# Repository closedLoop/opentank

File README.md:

# opentank
(WORK IN PROGRESS) A smart home sensor hub with ESP32-C6, rich analog capabilities, and full self-powering.
https://youtu.be/-s6jZ4U3TzU

## Design views

### Isometric 3D view

The render now uses repository-local models instead of machine-local CAD paths. U12 uses Espressif's exact manufacturer STEP model; J1, J2, and the previously missing small packages use footprint-aligned, datasheet-sized visualization models documented in [`assets/3d/README.md`](assets/3d/README.md). Confirm connector details and enclosure fit with exact manufacturer CAD before assembly release. The TH1 solder-wire footprint intentionally has no fitted component body.

### PCB top view

### PCB bottom view

### Schematic

## Changes versus `main`

These comparisons use matching KiCad layers, scale, and sheet coordinates. Magenta marks geometry present only on `main` (removed or moved), green marks geometry present only on this branch (added or moved), and gray provides unchanged context.

### PCB top comparison

### PCB bottom comparison

### Schematic comparison

## Important note

The USB D-/D+ routing and U17 SDA/SCL routing have been corrected in both the schematic and PCB. Both USB data pairs now remain on F.Cu without vias; the MCU-side pair is length tuned to 0.001 mm routed skew and assigned to a 0.127 mm / 0.150 mm USB width/gap net class targeting 90-ohm differential impedance.

The `templateforconfiguration.yaml` Home Assistant example is still somewhat broken because its current logic never reports a value below 0. `fulldevicecode.yaml` is the configuration programmed onto the PCB and has been observed running reliably for more than two months. Questions? Email rain@haaseindustries.com or comment on the linked YouTube video.

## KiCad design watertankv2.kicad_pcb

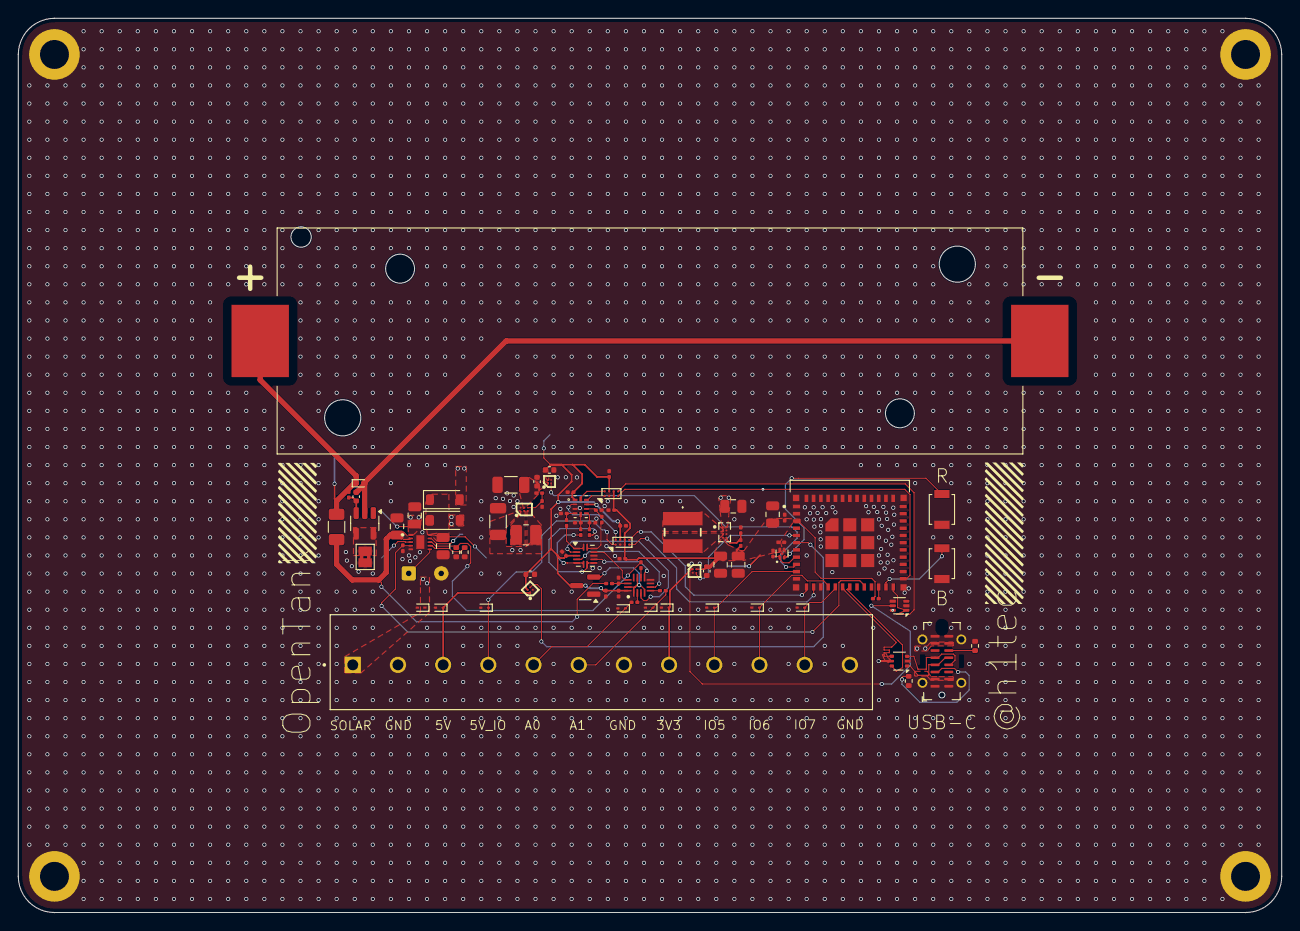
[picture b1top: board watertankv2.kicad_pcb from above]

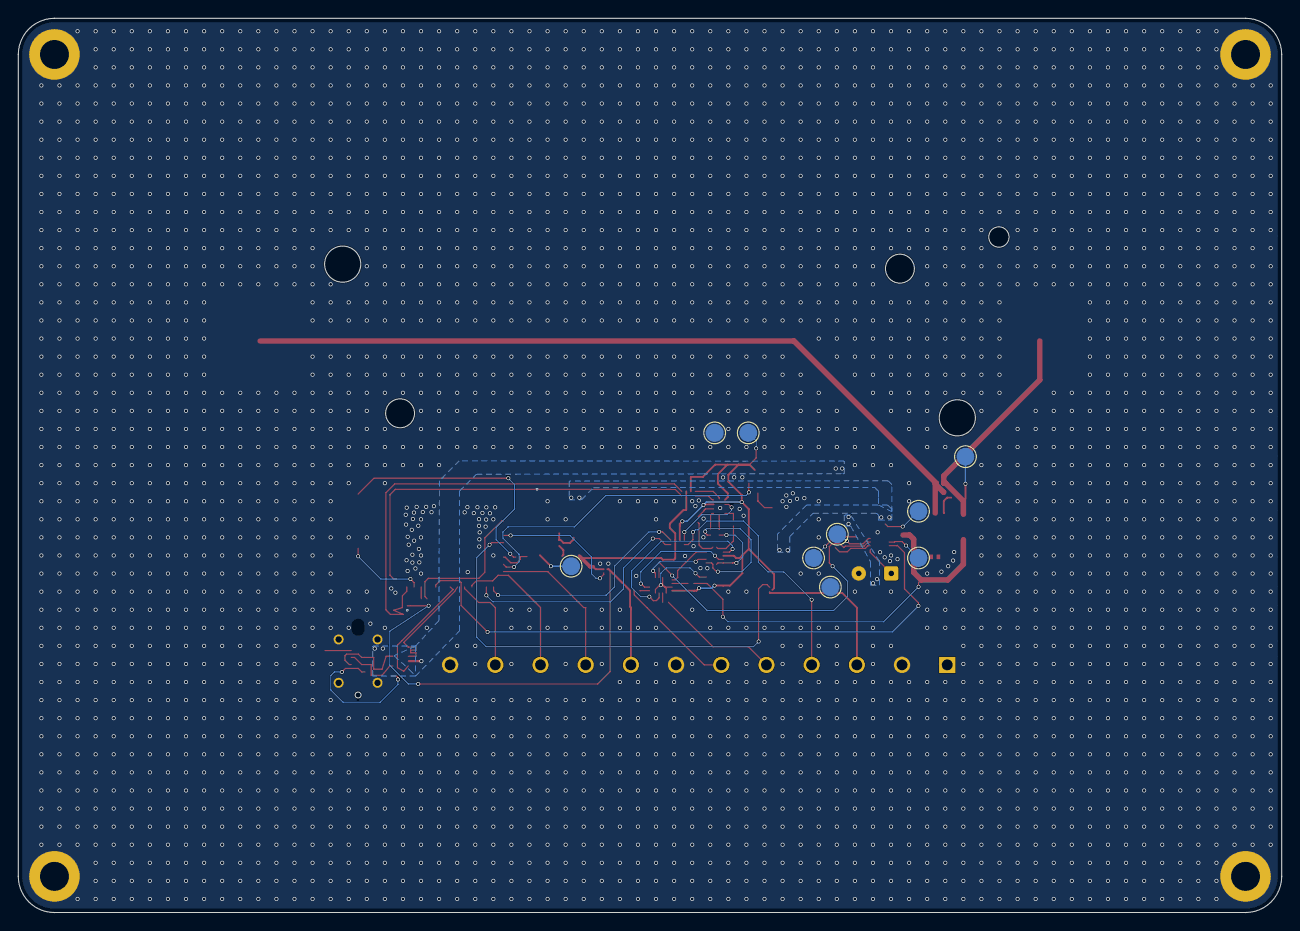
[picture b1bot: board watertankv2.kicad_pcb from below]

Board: 4 copper layers, 139.8 x 98.9 mm, 101 parts (9 on the bottom side), 69 nets.

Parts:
BT1: NMC; 21700holder
C1, C14, C15: 1u; C_0402_1005Metric
C2, C3, C4, C5, C6, C7, C23: 22u; C_0805_2012Metric
C8, C9: 10u; C_1206_3216Metric
C10, C11: 2u2; C_0402_1005Metric
C12, C13, C16, C17, C18, C19, C20, C21, C22, C24, C25, C26, C27, C28: 100n; C_0201_0603Metric
D1, D2: 20V; D_SOD-123
D3, D4, D5, D6, D7, D8, D9, D10, D11, D12: 6.5V; D_SOD-923
F1: 3A; Fuse_1206_3216Metric
H1, H2, H3, H4: 3.2mm; MountingHole_3.2mm_M3_DIN965_Pad
J1: 1792960; PHOENIX_1792960
J2: GT-USB-7051A; USB_C_Receptacle_G-Switch_GT-USB-7051x
JP1: I_SNSEXT; SolderJumper-2_P1.3mm_Bridged2Bar_Pad1.0x1.5mm
L1: 1u; 74404043010A
L2: 2u2; L_1008_2520Metric
R1, R9, R11, R12, R13: 100; R_0201_0603Metric
R2, R5, R15, R16: 511K; R_0201_0603Metric
R3: 6K8; R_0402_1005Metric
R4: 681; R_0402_1005Metric
R6: 91K; R_0201_0603Metric
R7: 1M1; R_0201_0603Metric
R8: 249K; R_0201_0603Metric
R10, R14, R17, R18, R19: 10K; R_0201_0603Metric
R23, R24: 5K1; R_0402_1005Metric
SW1: BOOT; SW_SPST_B3U-1000P
SW2: RESET; SW_SPST_B3U-1000P
TH1: 103AT; SolderWire-0.1sqmm_1x02_P3.6mm_D0.4mm_OD1mm
TP1: BQ_IN; TestPoint_Pad_D2.0mm
TP2: STAT1; TestPoint_Pad_D2.0mm
TP3: STAT2; TestPoint_Pad_D2.0mm
TP4: 3V3; TestPoint_Pad_D2.0mm
TP5, TP9: GND; TestPoint_Pad_D2.0mm
TP6: 5V; TestPoint_Pad_D2.0mm
TP7: SYS; TestPoint_Pad_D2.0mm
TP10: VBATSNS; TestPoint_Pad_D2.0mm
U1: DW03C; SOT-23-5
U2: BQ25185DLHR; IC_BQ25185DLHR
U3: TPS631010YBGR; IC_TPS631010YBGR
U4: TPS61099YFFR; BGA6C40P2X3_88X123X62
U5: TPS7A2050PYCKR; BGA4C35P2X2_62X62X33
U6, U11: TPS22916CYFPR; BGA4C40P2X2_75X75X50
U7: TMUX1511RSVR; QFN40P180X260X55-16N
U8: TLV9004IRUCR; Texas_S-PX2QFN-14
U9: TLV809EA46DBZR; SOT-23
U10: ADS1115IRUGR; IC_ADS1115IRUGR
U12: ESP32-C6-MINI-1U-N4; XCVR_ESP32-C6-MINI-1U-N4
U13, U14: LXS0102; Texas_DSBGA-8_0.9x1.9mm_Layout2x4_P0.5mm
U15: TLV803EA29DPWR; Texas_X2SON-5_0.8x0.8mm_P0.48mm
U16: USBLC6-2P6; SOT-666
U17: TMP102AIDRLR; SOT-563

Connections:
+3V3: C6.1, C7.1, C14.1, C22.2, C23.1, C24.2, C27.2, C28.2, R5.1, R18.1, R19.1, TP4.1, U3.D1 (VOUT), U6.A2 (VIN), U12.3 (3V3), U13.C1 (VCCA), U13.C2 (OE), U14.C1 (VCCA), U14.C2 (OE), U15.5 (VDD)
+5V: C11.1, C12.1, C13.1, C15.2, C20.2, C21.2, C25.2, C26.2, TP6.1, U5.A2 (OUT), U7.16 (VDD), U8.3 (V+), U9.3 (VDD), U10.1 (ADDR), U10.8 (VDD), U11.A2 (VIN), U13.B2 (VCCB), U14.B2 (VCCB)
/0: U12.12 (IO0), U14.D2 (A1)
/1: U12.13 (IO1), U14.D1 (A2)
/2: U6.B2 (ON), U12.5 (IO2)
/3: U11.B2 (ON), U12.6 (IO3)
/4: U5.B1 (EN), U12.9 (IO4)
/5: D6.1 (A1), J1.09, U12.10 (IO5)
/5V_IO: D7.1 (A1), J1.04, U14.A1 (B2)
/6: D10.1 (A1), J1.10, U12.15 (IO6)
/7: D11.1 (A1), J1.11, U12.16 (IO7)
/15: R2.1, U2.4 (~CE), U12.20 (IO15)
/18: U12.24 (IO18), U13.D2 (A1), U17.1 (SCL)
/19: U12.25 (IO19), U13.D1 (A2), U17.6 (SDA)
/ADS_0: C16.1, R9.2, U10.4 (AIN0)
/ADS_1: C17.1, R11.2, U10.5 (AIN1)
/ADS_2: C18.1, R12.2, U10.6 (AIN2)
/ADS_3: C19.1, R13.2, U10.7 (AIN3)
/ADS_A: U10.2 (ALERT/RDY), U14.A2 (B1)
/ADS_C: U10.10 (SCL), U13.A2 (B1)
/ADS_D: U10.9 (SDA), U13.A1 (B2)
/CH0: R10.2, U7.2 (S1)
/CH0_P: R9.1, U8.1 (-), U8.14
/CH1: R14.2, U7.5 (S2)
/CH1_P: R11.1, U8.5 (-), U8.6
/CH2: R17.2, U7.10 (S3)
/CH2_P: R12.1, U8.7, U8.8 (-)
/CH3: R15.2, R16.1, U7.14 (S4)
/CH3_P: R13.1, U8.12 (-), U8.13
/D+: J2.A6 (D+), J2.B6 (D+), U16.1 (I/O1)
/D-: J2.A7 (D-), J2.B7 (D-), U16.3 (I/O2)
/D_N: U12.17 (IO12), U16.4 (I/O2)
/D_P: U12.18 (IO13), U16.6 (I/O1)
/IN0: D8.1 (A1), J1.05, R10.1
/IN1: D4.1 (A1), J1.06, R14.1
/IS: R4.1, R17.1, U2.8 (ISET)
/PV: D2.2 (A), D5.1 (A1), J1.01
/SP3: D9.1 (A1), J1.08, U6.A1 (VOUT), U17.5 (V+)
/SP5: D3.1 (A1), J1.03, U11.A1 (VOUT)
/VBAT: C3.1, F1.1, R15.1, U2.2 (BAT)
/VBUS: D1.2 (A), J2.A4 (VBUS), J2.A9 (VBUS), J2.B4 (VBUS), J2.B9 (VBUS), U16.5 (VBUS)
/VSYS: C4.1, C5.1, C8.1, L2.1, TP7.1, U2.1 (SYS), U3.A1 (VIN), U3.A2 (EN), U4.A1 (VIN), U4.C1 (EN)
GND: C2.2, C3.2, C4.2, C5.2, C6.2, C7.2, C8.2, C9.2, C10.2, C11.2, C12.2, C13.2, C14.2, C15.1, C16.2, C17.2, C18.2, C19.2, C20.1, C21.1, C22.1, C23.2, C24.1, C25.1, C26.1, C27.1, C28.1, D3.2 (A2), D4.2 (A2), D5.2 (A2), D6.2 (A2), D7.2 (A2), D8.2 (A2), D9.2 (A2), D10.2 (A2), D11.2 (A2), H1.1, H2.1, H3.1, H4.1, J1.02, J1.07, J1.12, J2.A1 (GND), J2.A12 (GND), J2.B1 (GND), J2.B12 (GND), J2.S1 (SHIELD), JP1.1 (A), R2.2, R3.2, R4.2, R6.2, R8.1, R16.2, R23.2, R24.2, SW1.1 (A), SW2.1 (A), TH1.2, TP5.1, TP9.1, U2.5 (GND), U2.11 (THERMAL_PAD), U3.B2 (MODE), U3.C2 (GND), U4.A2 (GND), U5.B2 (GND), U6.B1 (GND), U7.8 (GND), U8.10 (V-), U9.1 (GND), U10.3 (GND), U11.B1 (GND), U12.1 (GND1), U12.2 (GND1__1), U12.11 (GND1__2), U12.14 (GND1__3), U12.36 (GND1__4), U12.37 (GND1__5), U12.38 (GND1__6), U12.39 (GND1__7), U12.40 (GND1__8), U12.41 (GND1__9), U12.42 (GND1__10), U12.43 (GND1__11), U12.44 (GND1__12), U12.45 (GND1__13), U12.46 (GND1__14), U12.47 (GND2), U12.48 (GND2__1), U12.49_1 (GND2__2), U12.49_2 (GND2__3), U12.49_3 (GND2__4), U12.49_4 (GND2__5), U12.49_5 (GND2__6), U12.49_6 (GND2__7), U12.49_7 (GND2__8), U12.49_8 (GND2__9), U12.49_9 (GND2__10), U12.50 (GND2__11), U12.51 (GND2__12), U12.52 (GND2__13), U12.53 (GND2__14), U13.B1 (GND), U14.B1 (GND), U15.3 (PAD), U15.4 (GND), U16.2 (GND), U17.2 (GND), U17.4 (ADD0)
unnamed: BT1.1 (+), D12.1 (A1), F1.2, R1.1, TP10.1
unnamed: BT1.2 (-), C1.2, D12.2 (A2), U1.2 (GND)
unnamed: C2.1, D1.1 (K), D2.1 (K), TP1.1, U2.10 (IN)
unnamed: J2.A5 (CC1), R24.1
unnamed: J2.B5 (CC2), R23.1
unnamed: JP1.2 (B), U1.4 (VM), U1.5 (VM)
unnamed: SW1.2 (B), U12.23 (IO9)
unnamed: SW2.2 (B), U15.2 (MR_N)
unnamed: C1.1, R1.2, U1.3 (VDD)
unnamed: R3.1, U2.7 (ILIM/VSET)
unnamed: TP2.1, U2.9 (STAT1)
unnamed: TP3.1, U2.3 (STAT2)
unnamed: TH1.1, U2.6 (TS/MR)
unnamed: R5.2, R6.1, U3.D2 (FB)
unnamed: L1.1, U3.B1 (LX1)
unnamed: L1.2, U3.C1 (LX2)
unnamed: R7.1, R8.2, U4.C2 (FB)
unnamed: L2.2, U4.B1 (SW)
unnamed: C9.1, C10.1, R7.2, U4.B2 (VOUT), U5.A1 (IN)
unnamed: U7.3 (D1), U8.2 (+)
unnamed: U7.6 (D2), U8.4 (+)
unnamed: U7.9 (D3), U8.9 (+)
unnamed: U7.13 (D4), U8.11 (+)
unnamed: U7.1 (SEL1), U7.4 (SEL2), U7.11 (SEL3), U7.15 (SEL4), U9.2 (*RESET)
unnamed: R19.2, U12.8 (EN), U15.1 (RESET_N)
unnamed: R18.2, U12.22 (IO8)
